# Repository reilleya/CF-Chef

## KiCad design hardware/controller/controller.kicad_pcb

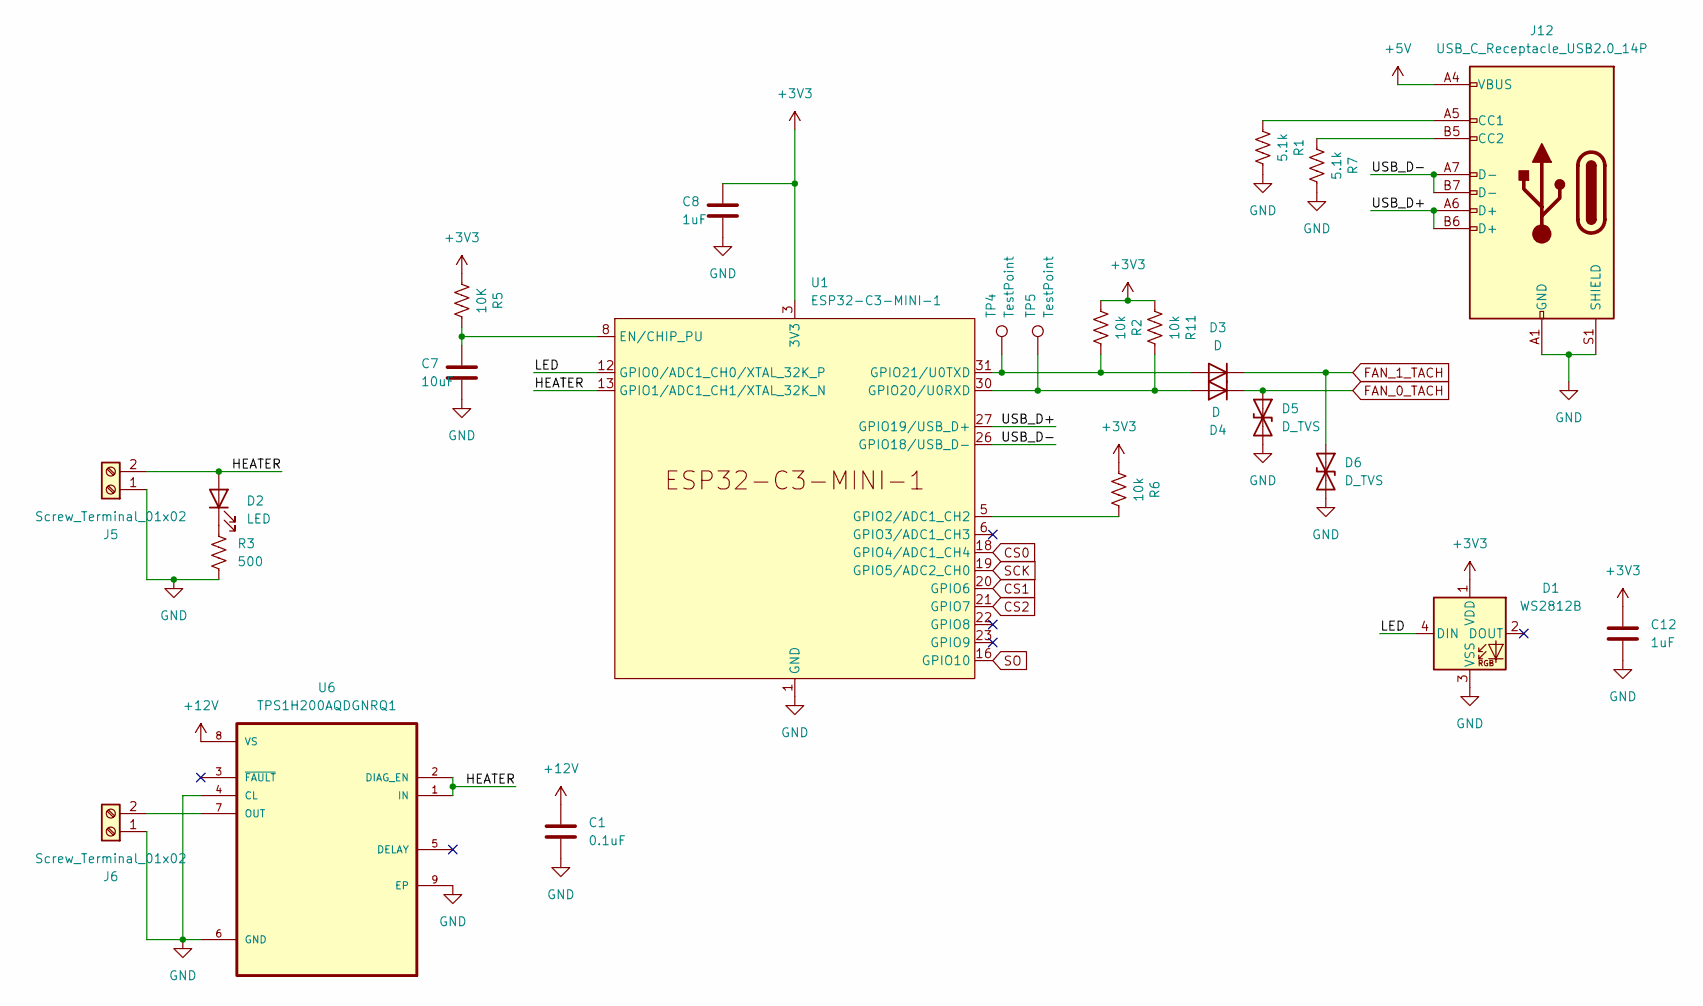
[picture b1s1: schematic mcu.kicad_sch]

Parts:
C1: 0.1uF; C_0805_2012Metric; LCSC C49678
C7: 10uF; C_0805_2012Metric; LCSC` C15850
C8, C12: 1uF; C_0805_2012Metric; LCSC C28323
D1: WS2812B; LED_WS2812B_PLCC4_5.0x5.0mm_P3.2mm; LCSC C2874885
D2: LED; LED_0805_2012Metric; LCSC C84256
D3, D4: D; TSOT-23; LCSC C14308
D5, D6: D_TVS; D_SOD-323F; LCSC C502541
J5, J6: Screw_Terminal_01x02; TerminalBlock_4Ucon_1x02_P3.50mm_Horizontal
J12: USB_C_Receptacle_USB2.0_14P; USB_C_Receptacle_GCT_USB4105-xx-A_16P_TopMnt_Horizontal; LCSC C2765186
R1, R7: 5.1k; R_0805_2012Metric; LCSC C27834
R2, R6, R11: 10k; R_0805_2012Metric; LCSC C84376
R3: 500; R_0805_2012Metric; LCSC C2828857
R5: 10K; R_0805_2012Metric; LCSC C84376
TP4, TP5: TestPoint; TestPoint_THTPad_2.0x2.0mm_Drill1.0mm
U1: ESP32-C3-MINI-1; LCSC C2838502
U6: TPS1H200AQDGNRQ1; SOP65P490X110-9N; LCSC C2653785

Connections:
+3V3: C8.1, C12.1, D1.1 (VDD), R2.2, R5.2, R6.2, R11.2, U1.3 (3V3); also elsewhere on the board
+5V: J12.A4 (VBUS), J12.A9 (VBUS), J12.B4 (VBUS), J12.B9 (VBUS); also elsewhere on the board
+12V: C1.1, U6.8 (VS); also elsewhere on the board
/Microcontroller/HEATER: D2.2 (A), J5.2, U1.13 (GPIO1/ADC1_CH1/XTAL_32K_N), U6.1 (IN), U6.2 (DIAG_EN)
/Microcontroller/LED: D1.4 (DIN), U1.12 (GPIO0/ADC1_CH0/XTAL_32K_P)
/Microcontroller/USB_D+: J12.A6 (D+), J12.B6 (D+), U1.27 (GPIO19/USB_D+)
/Microcontroller/USB_D-: J12.A7 (D-), J12.B7 (D-), U1.26 (GPIO18/USB_D-)
CS0: U1.18 (GPIO4/ADC1_CH4); also elsewhere on the board
CS1: U1.20 (GPIO6); also elsewhere on the board
CS2: U1.21 (GPIO7); also elsewhere on the board
FAN_0_TACH: D4.3 (K), D5.1 (A1); also elsewhere on the board
FAN_1_TACH: D3.3 (K), D6.1 (A1); also elsewhere on the board
GND: C1.2, C7.2, C8.2, C12.2, D1.3 (VSS), D5.2 (A2), D6.2 (A2), J5.1, J6.1, J12.A1 (GND), J12.A12 (GND), J12.B1 (GND), J12.B12 (GND), J12.S1 (SHIELD), R1.1, R3.2, R7.1, U1.1 (GND), U1.2 (GND), U1.11 (GND), U1.14 (GND), U1.36 (GND), U1.37 (GND), U1.38 (GND), U1.39 (GND), U1.40 (GND), U1.41 (GND), U1.42 (GND), U1.43 (GND), U1.44 (GND), U1.45 (GND), U1.46 (GND), U1.47 (GND), U1.48 (GND), U1.49 (GND), U1.50 (GND), U1.51 (GND), U1.52 (GND), U1.53 (GND), U6.4 (CL), U6.6 (GND), U6.9 (EP); also elsewhere on the board
unnamed: D2.1 (K), R3.1
unnamed: D3.1 (A), R2.1, TP4.1, U1.31 (GPIO21/U0TXD)
unnamed: D4.1 (A), R11.1, TP5.1, U1.30 (GPIO20/U0RXD)
unnamed: J6.2, U6.7 (OUT)
unnamed: J12.A5 (CC1), R1.2
unnamed: J12.B5 (CC2), R7.2
unnamed: C7.1, R5.1, U1.8 (EN/CHIP_PU)
unnamed: R6.1, U1.5 (GPIO2/ADC1_CH2)
SCK: U1.19 (GPIO5/ADC2_CH0); also elsewhere on the board
SO: U1.16 (GPIO10); also elsewhere on the board

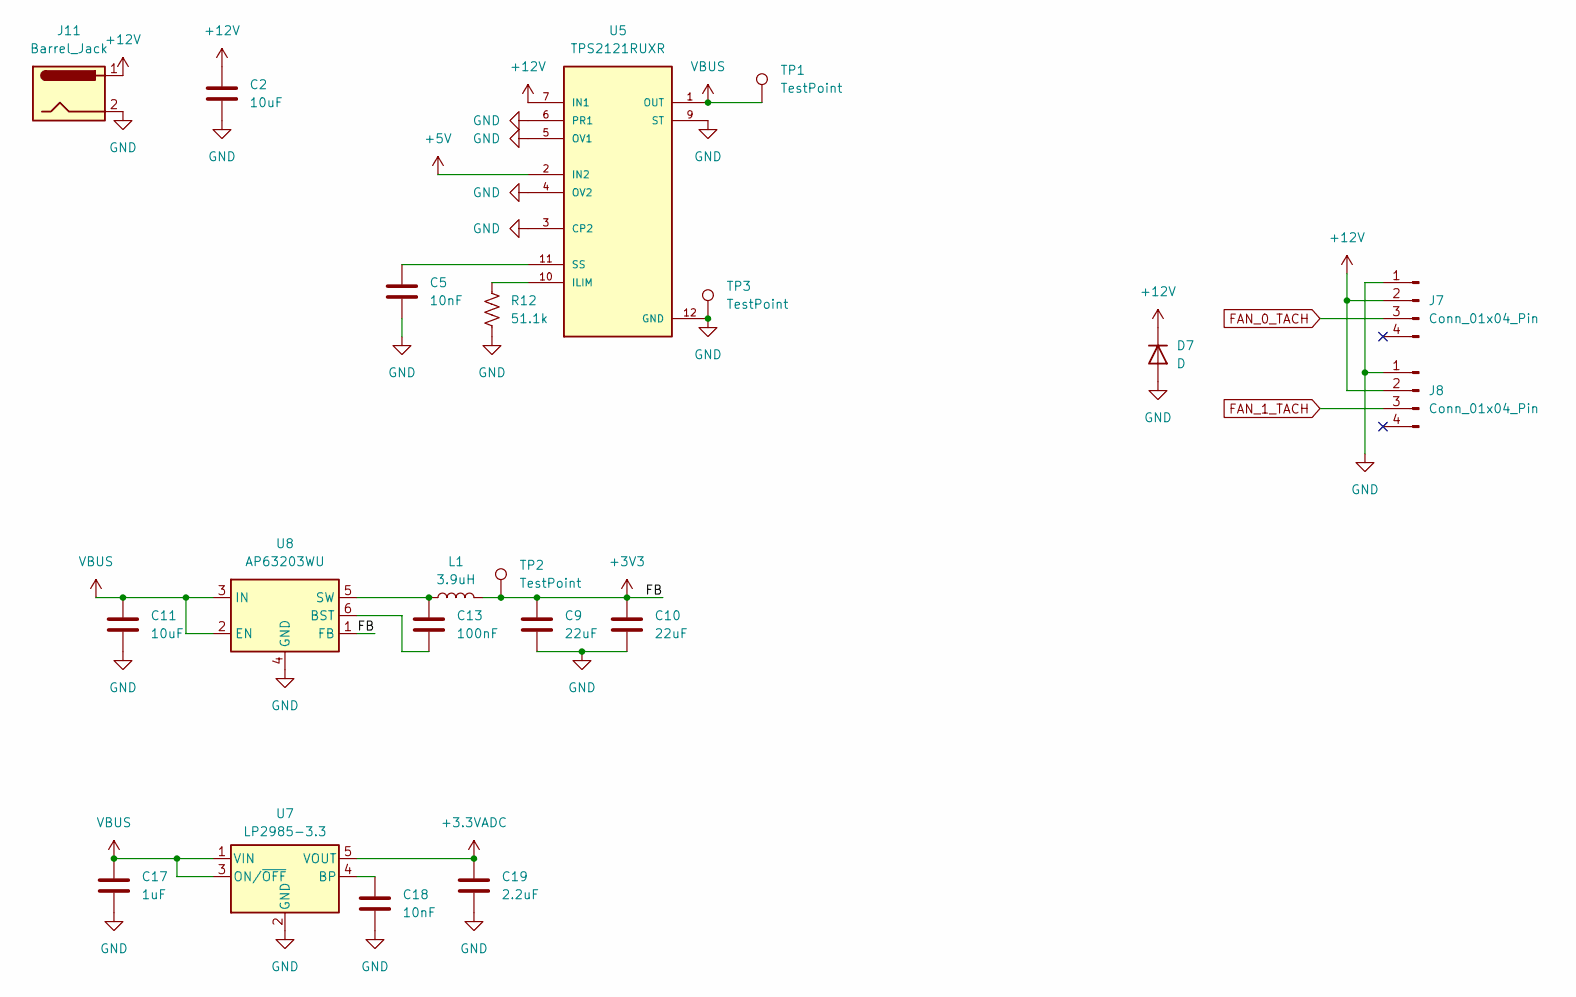
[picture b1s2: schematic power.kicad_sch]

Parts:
C2, C11: 10uF; C_0805_2012Metric; LCSC C15850
C5, C18: 10nF; C_0805_2012Metric; LCSC C1710
C9, C10: 22uF; C_0805_2012Metric; LCSC C5674
C13: 100nF; C_0805_2012Metric; LCSC C1711
C17: 1uF; C_0805_2012Metric; LCSC C28323
C19: 2.2uF; C_0805_2012Metric; LCSC C377773
D7: D; D_SMA; LCSC C445494
J7, J8: Conn_01x04_Pin; FanPinHeader_1x04_P2.54mm_Vertical
J11: Barrel_Jack; BarrelJack_CUI_PJ-063AH_Horizontal
L1: 3.9uH; L_APV_ANR3015; LCSC C42429305
R12: 51.1k; R_0805_2012Metric; LCSC C17731
TP1, TP2, TP3: TestPoint; TestPoint_THTPad_2.0x2.0mm_Drill1.0mm
U5: TPS2121RUXR; IC_TPS2121RUXR; LCSC C485916
U7: LP2985-3.3; SOT-23-5; LCSC C95414
U8: AP63203WU; TSOT-23-6; LCSC C780769

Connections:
+3.3VADC: C19.1, U7.5 (VOUT); also elsewhere on the board
+3V3: C9.1, C10.1, L1.2, TP2.1, U8.1 (FB); also elsewhere on the board
+5V: U5.2 (IN2), U5.2_1 (IN2); also elsewhere on the board
+12V: C2.1, D7.1 (K), J7.2, J8.2, J11.1, U5.7 (IN1), U5.7_1 (IN1); also elsewhere on the board
FAN_0_TACH: J7.3; also elsewhere on the board
FAN_1_TACH: J8.3; also elsewhere on the board
GND: C2.2, C5.2, C9.2, C10.2, C11.2, C17.2, C18.2, C19.2, D7.2 (A), J7.1, J8.1, J11.2, R12.2, TP3.1, U5.3 (CP2), U5.4 (OV2), U5.5 (OV1), U5.6 (PR1), U5.9 (ST), U5.12 (GND), U7.2 (GND), U8.4 (GND); also elsewhere on the board
unnamed: R12.1, U5.10 (ILIM)
unnamed: C5.1, U5.11 (SS)
unnamed: C18.1, U7.4 (BP)
unnamed: C13.2, U8.6 (BST)
unnamed: C13.1, L1.1, U8.5 (SW)
VBUS: C11.1, C17.1, TP1.1, U5.1 (OUT), U5.1_1 (OUT), U5.8 (OUT), U5.8_1 (OUT), U7.1 (VIN), U7.3 (ON/~OFF), U8.2 (EN), U8.3 (IN)

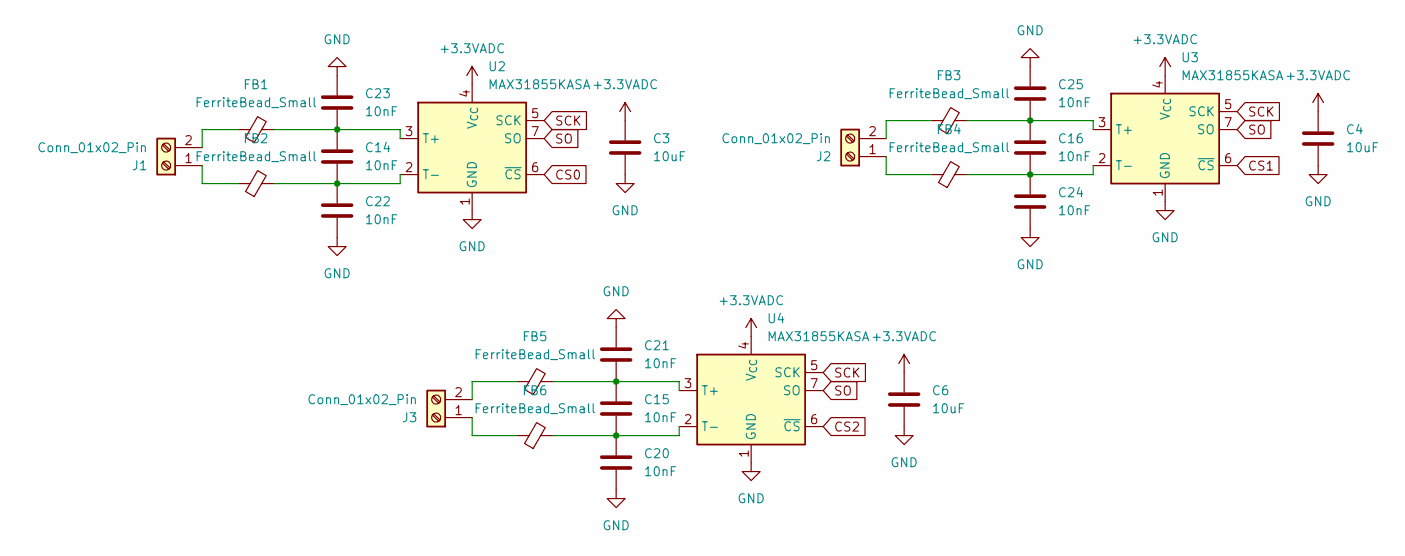
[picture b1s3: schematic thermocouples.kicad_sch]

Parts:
C3, C4, C6: 10uF; C_0805_2012Metric; LCSC C15850
C14, C15, C16, C20, C21, C22, C23, C24, C25: 10nF; C_0805_2012Metric; LCSC C1710
FB1, FB2, FB3, FB4, FB5, FB6: FerriteBead_Small; C_0805_2012Metric; LCSC C397304
J1, J2, J3: Conn_01x02_Pin; TerminalBlock_4Ucon_1x02_P3.50mm_Horizontal
U2, U3, U4: MAX31855KASA; SOIC-8_3.9x4.9mm_P1.27mm; LCSC C52028

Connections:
+3.3VADC: C3.1, C4.1, C6.1, U2.4 (V_{CC}), U3.4 (V_{CC}), U4.4 (V_{CC}); also elsewhere on the board
CS0: U2.6 (~CS); also elsewhere on the board
CS1: U3.6 (~CS); also elsewhere on the board
CS2: U4.6 (~CS); also elsewhere on the board
GND: C3.2, C4.2, C6.2, C20.2, C21.1, C22.2, C23.1, C24.2, C25.1, U2.1 (GND), U3.1 (GND), U4.1 (GND); also elsewhere on the board
unnamed: FB2.1, J1.1
unnamed: FB1.1, J1.2
unnamed: FB4.1, J2.1
unnamed: FB3.1, J2.2
unnamed: FB6.1, J3.1
unnamed: FB5.1, J3.2
unnamed: C14.1, C23.2, FB1.2, U2.3 (T+)
unnamed: C14.2, C22.1, FB2.2, U2.2 (T-)
unnamed: C16.1, C25.2, FB3.2, U3.3 (T+)
unnamed: C16.2, C24.1, FB4.2, U3.2 (T-)
unnamed: C15.1, C21.2, FB5.2, U4.3 (T+)
unnamed: C15.2, C20.1, FB6.2, U4.2 (T-)
SCK: U2.5 (SCK), U3.5 (SCK), U4.5 (SCK); also elsewhere on the board
SO: U2.7 (SO), U3.7 (SO), U4.7 (SO); also elsewhere on the board

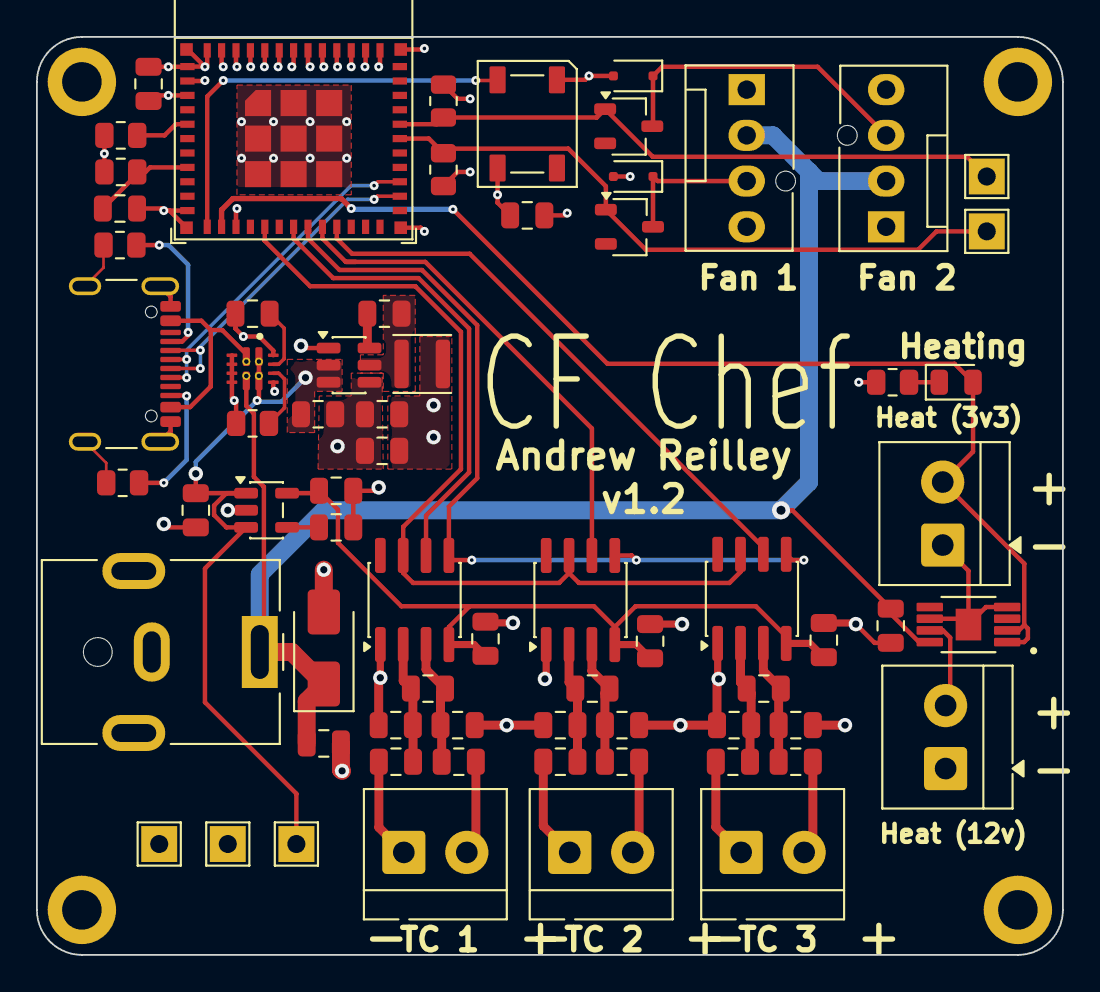
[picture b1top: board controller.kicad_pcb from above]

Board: 4 copper layers, 57.0 x 51.0 mm, 73 parts (0 on the bottom side), 42 nets.

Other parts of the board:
H1, H2, H3, H4: MountingHole; MountingHole_2.2mm_M2_ISO14580_Pad

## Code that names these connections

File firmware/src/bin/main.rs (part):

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
    // Set up LED
    let rmt = esp_hal::rmt::Rmt::new(peripherals.RMT, Rate::from_mhz(80)).unwrap();
    let rmt_output = Output::new(peripherals.GPIO0, Level::Low, Default::default());
    let mut led = lib::led::Led {
        pixel_buffer: [lib::led::Rgb { r: 0, g: 0, b: 0 }; 1],
        rmt_channel: Some(lib::led::Led::configure_rmt(rmt, rmt_output)),
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
    let mut fan_tachs = [
        Input::new(
            peripherals.GPIO20,
            InputConfig::default().with_pull(Pull::Up),
        ),
        Input::new(
            peripherals.GPIO21,
            InputConfig::default().with_pull(Pull::Up),
        ),
    ];
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    }

    // Set up heater output
    let mut heater_output = Output::new(peripherals.GPIO1, Level::Low, OutputConfig::default());

    // Set up SPI bus for MAX31855 thermocouples
    let mut spi_bus = Spi::new(
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            .with_mode(SpiMode::_0),
    )
    .unwrap()
    .with_sck(peripherals.GPIO5)
    .with_miso(peripherals.GPIO10);
    let mut spi_cs_pins: [Output; lib::constants::NUM_THERMOCOUPLES] = [
        Output::new(peripherals.GPIO4, Level::High, OutputConfig::default()),
        Output::new(peripherals.GPIO6, Level::High, OutputConfig::default()),
        Output::new(peripherals.GPIO7, Level::High, OutputConfig::default()),
    ];

    let timg0 = TimerGroup::new(peripherals.TIMG0);
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
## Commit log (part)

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2026-01-19 Bring up LED
2026-02-07 Add functions for interpreting MAX31855 reads
2026-02-08 Make webserver state atomic
2026-02-08 Pre-state-machine prototype of simple oven run
2026-02-11 Read zone temperatures in a loop, include in state object
2026-02-11 Cleanup
2026-02-15 Replace input diodes with power mux chip
2026-02-15 Swap out voltage regulator
2026-02-15 Widen board and add polarity labels to heater outputs
2026-02-23 Move 12v out from under TC chips
2026-02-24 Update inductor to match regulator spec better
2026-03-03 Move control loop to state machine structure
2026-03-03 Check for faults in enabled TCs
2026-03-07 1.1 production tweaks
2026-03-08 Protect fan tach inputs
2026-03-08 Add TVS diode to 12V rail
2026-03-18 Reroute regulator
2026-03-19 Increase via size for manufacturing
2026-03-20 Fix power mux rotation
2026-03-27 Change SSID
2026-03-30 Fix diode footprints
2026-04-01 Reset LED color immediately on startup
2026-04-01 Include time since last fan edge in status
2026-04-04 Read fan speed and include it in status
2026-04-04 Monitor for fan faults and include in status
2026-04-04 Handle fans in loop
2026-04-04 Show faults in webapp
2026-04-09 Switch from form submission to json
2026-04-09 Clean up web state/extraction
2026-05-03 Add cure schedules with ramps and holds
2026-05-06 Clean up CSS
2026-05-08 Show state in web app
2026-05-08 Add prototype of system status box
2026-05-13 Add filtering caps to thermocouples
2026-05-29 Add thermocouple offsets
2026-06-11 Add configurable temperature bounds
2026-06-11 Fix negative thermocouple readings
2026-06-18 Improve progress/time output
2026-06-23 Fix high SPI clock speed leading to occasional bad TC readings
2026-06-24 Add linear regulator for MAX chips
2026-06-25 Increase capacitance of MAX caps
